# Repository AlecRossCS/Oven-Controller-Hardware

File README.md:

# Oven-Controller-Hardware
This project is about creating a controller for a heating element for a custom designed oven. The temperature needs to be controlled with industrial precision, so this baord contains a microcontroller as well as devices needed to interact with a thermocouple to precisely sense temperature, as well as a large power mosfet, which controls the power to the heating element to control the temperature with great accuracy. 

# Design

because of the supply shortage, the microcontroller was chosen as a RP2040 already made onto a Raspberry pi Pico board, because that board can be soldered onto another, as in this case, and both the RP2040, and my second choice of STM32F0 controllers are impossible to buy for any project currently. So buying a premade micro offers flexability as you can buy them in the quantities I need. the Micro interacts with both the sensor and mosfet, as well as capability to drive an LCD screen for display. A notable thing that is different here is that the mosfet does not use a large heatsink. That is not because it does not disspate much power, but because the newer technology on the market allows the Vishay thermal jumper to absorb and funnel much of the heat directly from the heat fin into the ground plane.

# Hardware
this was a standard layout, fairly straight forward. as components were placed and grouped, and then power connections ran, and then the rest of the connections, and then a gnd plane. 

the mockup

Version 1 has already been manufactured, and is currently in the firmware design stage. The major differences in design from version 1 is that it had SMPS on th board, which has now been broken into a separate board to allow for better space usage, a smaller footprint, and better thermal design for the SMPS.

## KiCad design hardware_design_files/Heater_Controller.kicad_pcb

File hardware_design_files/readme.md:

# hardware designfiles
all files designed in kicad, and simulated in Pspice.

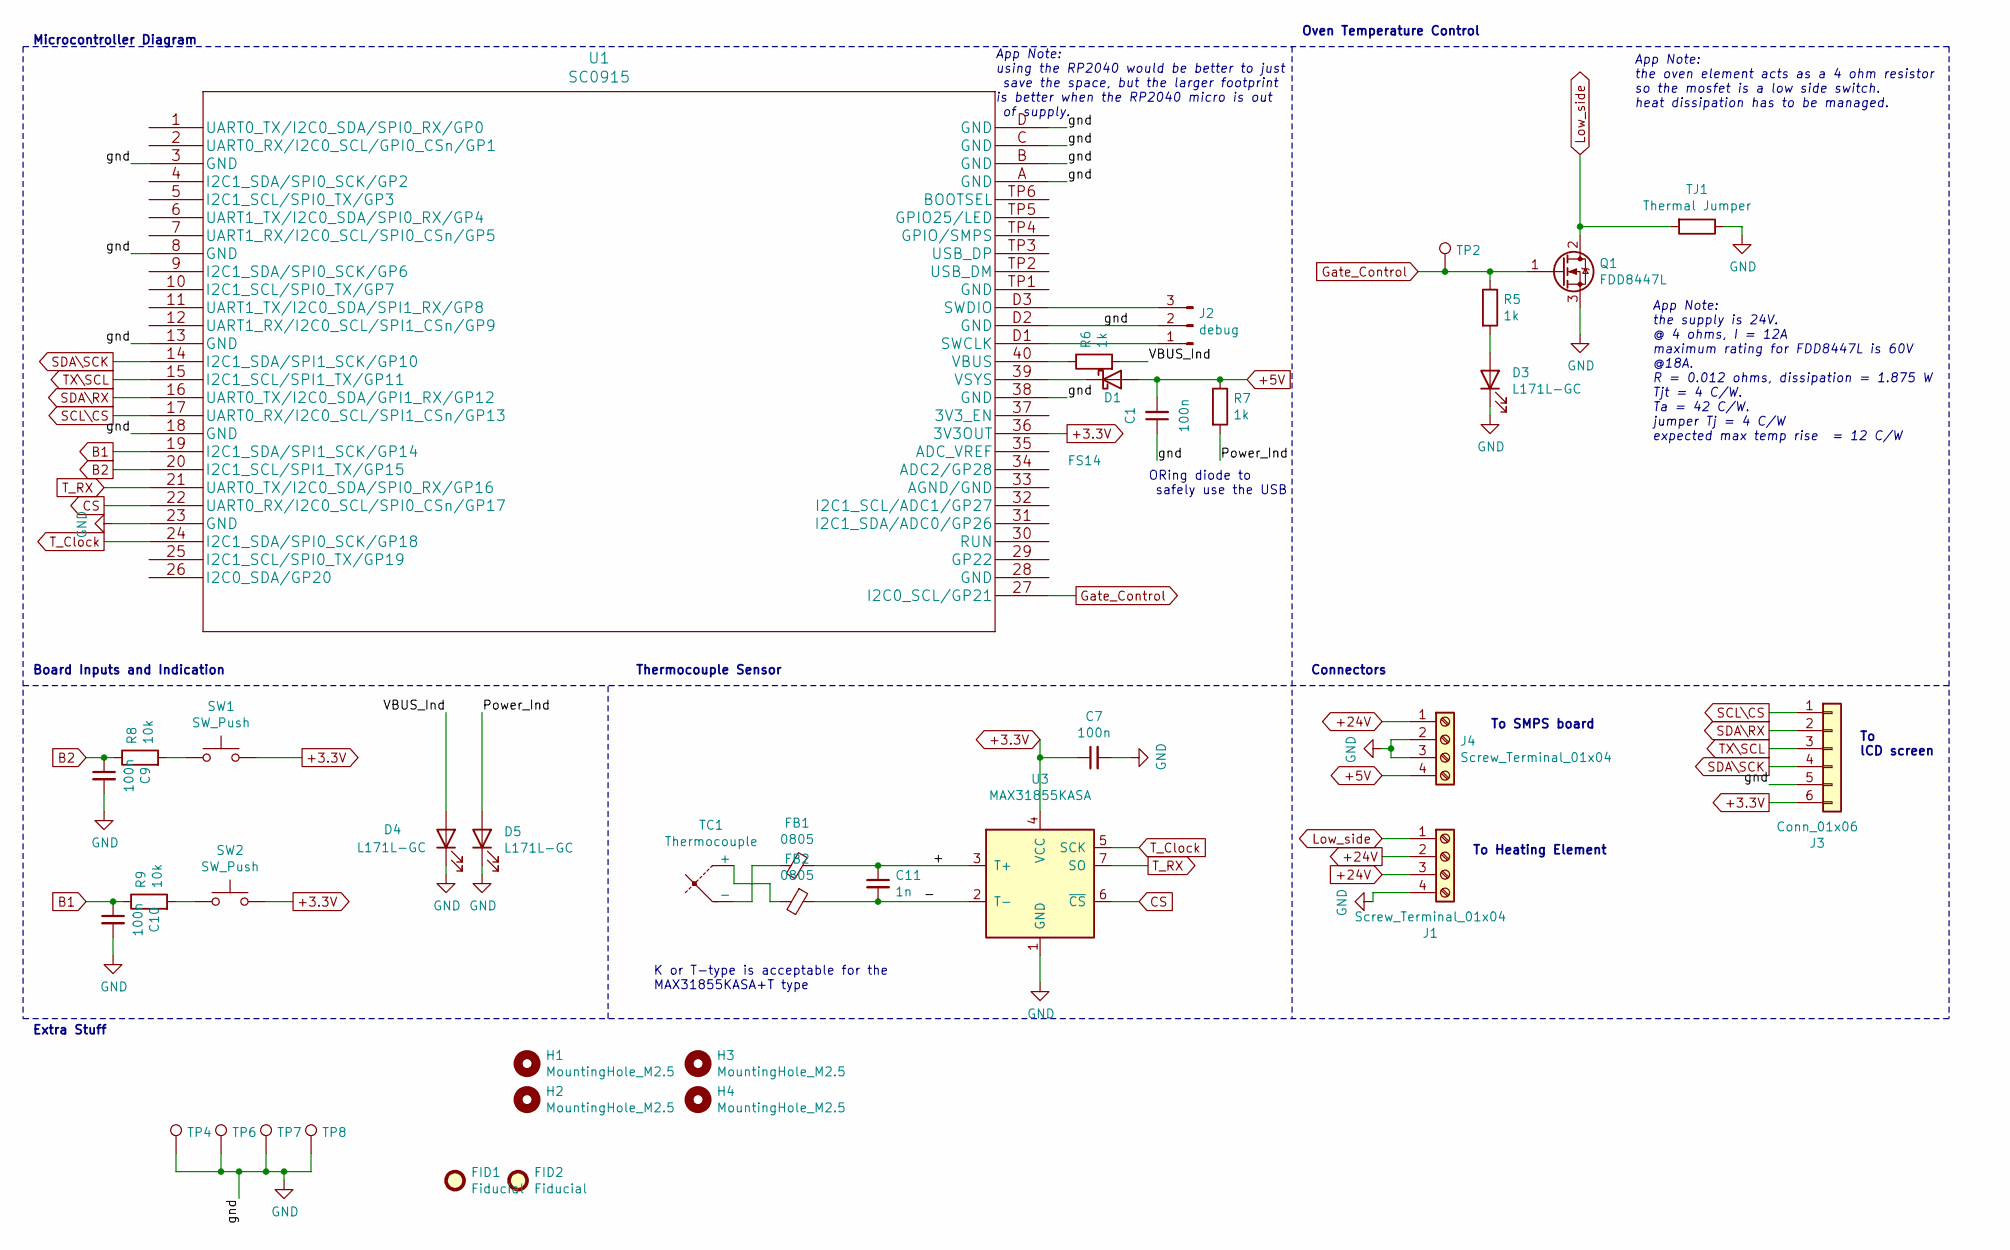
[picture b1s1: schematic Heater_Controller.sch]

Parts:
C1, C7, C9, C10: 100n; C_0805_2012Metric_Pad1.18x1.45mm_HandSolder
C11: 1n; C_0603_1608Metric_Pad1.08x0.95mm_HandSolder
D1: FS14; D_SOD-123F
D3, D4, D5: L171L-GC; LED_1206_3216Metric_Pad1.42x1.75mm_HandSolder
FB1, FB2: 0805; R_0805_2012Metric_Pad1.20x1.40mm_HandSolder
FID1, FID2: Fiducial; Fiducial_0.75mm_Mask1.5mm
H1, H2, H3, H4: MountingHole_M2.5; MountingHole_2.7mm_M2.5_ISO7380_Pad_TopBottom
J1: Screw_Terminal_01x04; TerminalBlock_bornier-4_P5.08mm
J2: debug; PinHeader_1x03_P2.54mm_Vertical
J3: Conn_01x06; PinHeader_1x06_P2.54mm_Vertical
J4: Screw_Terminal_01x04; TerminalBlock_TE_282834-4_1x04_P2.54mm_Horizontal
Q1: FDD8447L; TO-252-3_TabPin2
R5, R6, R7: 1k; R_0805_2012Metric_Pad1.20x1.40mm_HandSolder
R8, R9: 10k; R_0805_2012Metric_Pad1.20x1.40mm_HandSolder
SW1, SW2: SW_Push; SW_SPST_TL3305C
TC1: Thermocouple; TerminalBlock_Phoenix_MKDS-1,5-2_1x02_P5.00mm_Horizontal
TJ1: Thermal Jumper; R_1206_3216Metric_Pad1.30x1.75mm_HandSolder
TP2, TP4, TP6, TP7, TP8: TestPoint_Keystone_5019_Minature
U1: SC0915; SC0915-Up
U3: MAX31855KASA; SOIC-8_3.9x4.9mm_P1.27mm

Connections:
+3.3V: C7.1, J3.6, SW1.2, SW2.2, U1.36 (3V3OUT), U3.4 (VCC)
+5V: C1.2, D1.2 (A), J4.4, R7.1
+24V: J1.2, J1.3, J4.1
/+: C11.1, FB1.2, U3.3 (T+)
/-: C11.2, FB2.1, U3.2 (T-)
/Power_Ind: D5.2 (A), R7.2
/VBUS_Ind: D4.2 (A), R6.2
B1: C10.1, R9.1, U1.19 (I2C1_SDA/SPI1_SCK/GP14)
B2: C9.1, R8.1, U1.20 (I2C1_SCL/SPI1_TX/GP15)
CS: U1.22 (UART0_RX/I2C0_SCL/SPI0_CSn/GP17), U3.6 (~CS~)
GND: C1.1, C7.2, C9.2, C10.2, D3.1 (K), D4.1 (K), D5.1 (K), J1.4, J2.2, J3.5, J4.2, J4.3, Q1.3 (S), TJ1.1, TP4.1, TP6.1, TP7.1, TP8.1, U1.3 (GND), U1.8 (GND), U1.13 (GND), U1.18 (GND), U1.23 (GND), U1.38 (GND), U1.A (GND), U1.B (GND), U1.C (GND), U1.D (GND), U1.D2 (GND), U3.1 (GND)
Gate_Control: Q1.1 (G), R5.1, TP2.1, U1.27 (I2C0_SCL/GP21)
Low_side: J1.1, Q1.2 (D), TJ1.2
unnamed: D1.1 (K), U1.39 (VSYS)
unnamed: D3.2 (A), R5.2
unnamed: FB1.1, TC1.2 (-)
unnamed: FB2.2, TC1.1 (+)
unnamed: J2.1, U1.D1 (SWCLK)
unnamed: J2.3, U1.D3 (SWDIO)
unnamed: R6.1, U1.40 (VBUS)
unnamed: R8.2, SW1.1
unnamed: R9.2, SW2.1
SCL\CS: J3.1, U1.17 (UART0_RX/I2C0_SCL/SPI1_CSn/GP13)
SDA\RX: J3.2, U1.16 (UART0_TX/I2C0_SDA/GPI1_RX/GP12)
SDA\SCK: J3.4, U1.14 (I2C1_SDA/SPI1_SCK/GP10)
TX\SCL: J3.3, U1.15 (I2C1_SCL/SPI1_TX/GP11)
T_Clock: U1.24 (I2C1_SDA/SPI0_SCK/GP18), U3.5 (SCK)
T_RX: U1.21 (UART0_TX/I2C0_SDA/SPI0_RX/GP16), U3.7 (SO)

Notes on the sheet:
K or T-type is acceptable for the MAX31855KASA+T type
ORing diode to safely use the USB
Microcontroller Diagram
Board Inputs and Indication
Thermocouple Sensor
App Note: using the RP2040 would be better to just save the space, but the larger footprint is better when the RP2040 micro is out of supply.
Oven Temperature Control
App Note: the oven element acts as a 4 ohm resistor so the mosfet is a low side switch. heat dissipation has to be managed.
App Note: the supply is 24V. @ 4 ohms, I = 12A maximum rating for FDD8447L is 60V @18A. R = 0.012 ohms, dissipation = 1.875 W Tjt = 4 C/W. Ta = 42 C/W. jumper Tj = 4 C/W expected max temp rise = 12 C/W
Connectors
To SMPS board
To Heating Element
To lCD screen
Extra Stuff

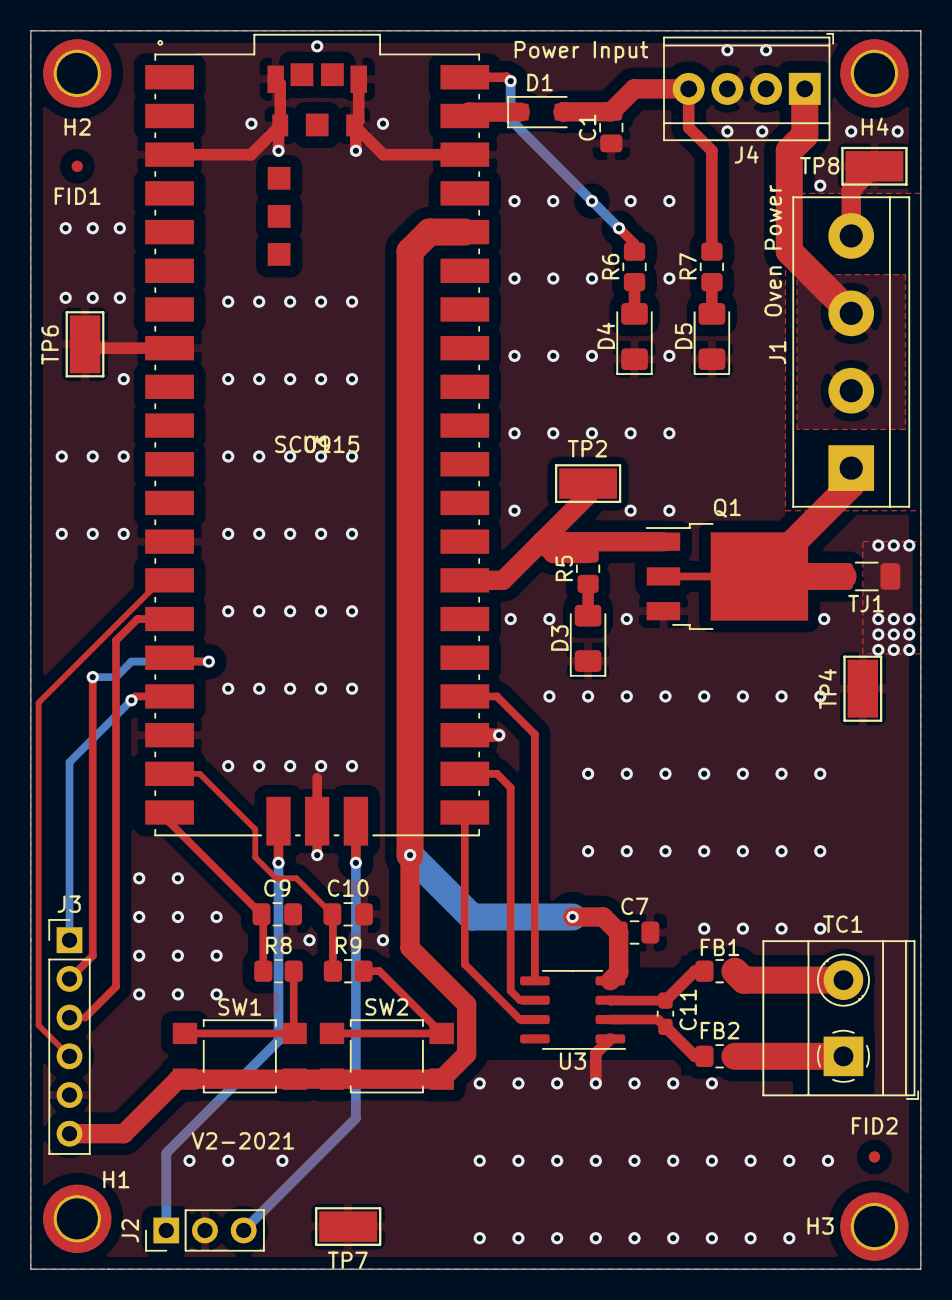
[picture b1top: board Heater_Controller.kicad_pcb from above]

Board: 2 copper layers, 58.4 x 81.3 mm, 38 parts (0 on the bottom side), 28 nets.

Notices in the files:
parts and their libraries:
Copyright 2021 Accelerated Designs. All rights reserved.
